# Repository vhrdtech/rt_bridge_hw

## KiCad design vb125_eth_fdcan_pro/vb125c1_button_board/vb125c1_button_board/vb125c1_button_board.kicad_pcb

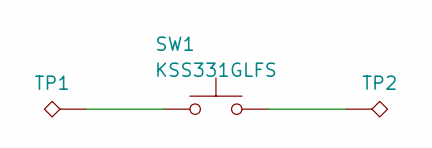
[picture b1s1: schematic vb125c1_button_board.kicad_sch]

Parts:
SW1: KSS331GLFS; SW_KSS3
TP1, TP2: TestPoint_Alt; TestPoint_Pad_4.0x4.0mm

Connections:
unnamed: SW1.1, TP1.1
unnamed: SW1.2, TP2.1

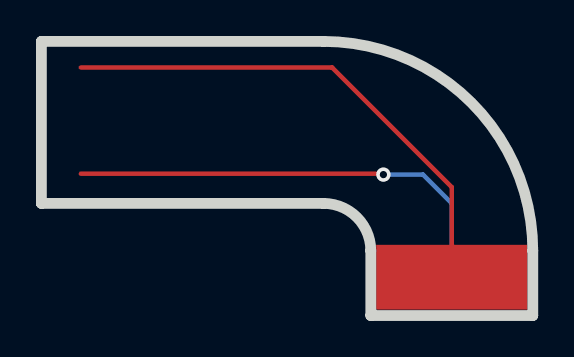
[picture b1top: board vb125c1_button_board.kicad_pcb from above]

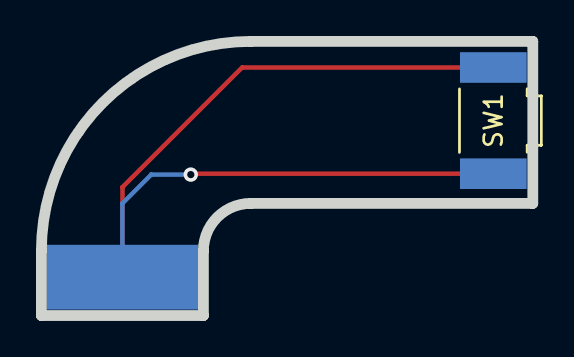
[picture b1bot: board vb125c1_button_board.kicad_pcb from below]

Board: 2 copper layers, 27.3 x 15.2 mm, 3 parts (2 on the bottom side), 2 nets.

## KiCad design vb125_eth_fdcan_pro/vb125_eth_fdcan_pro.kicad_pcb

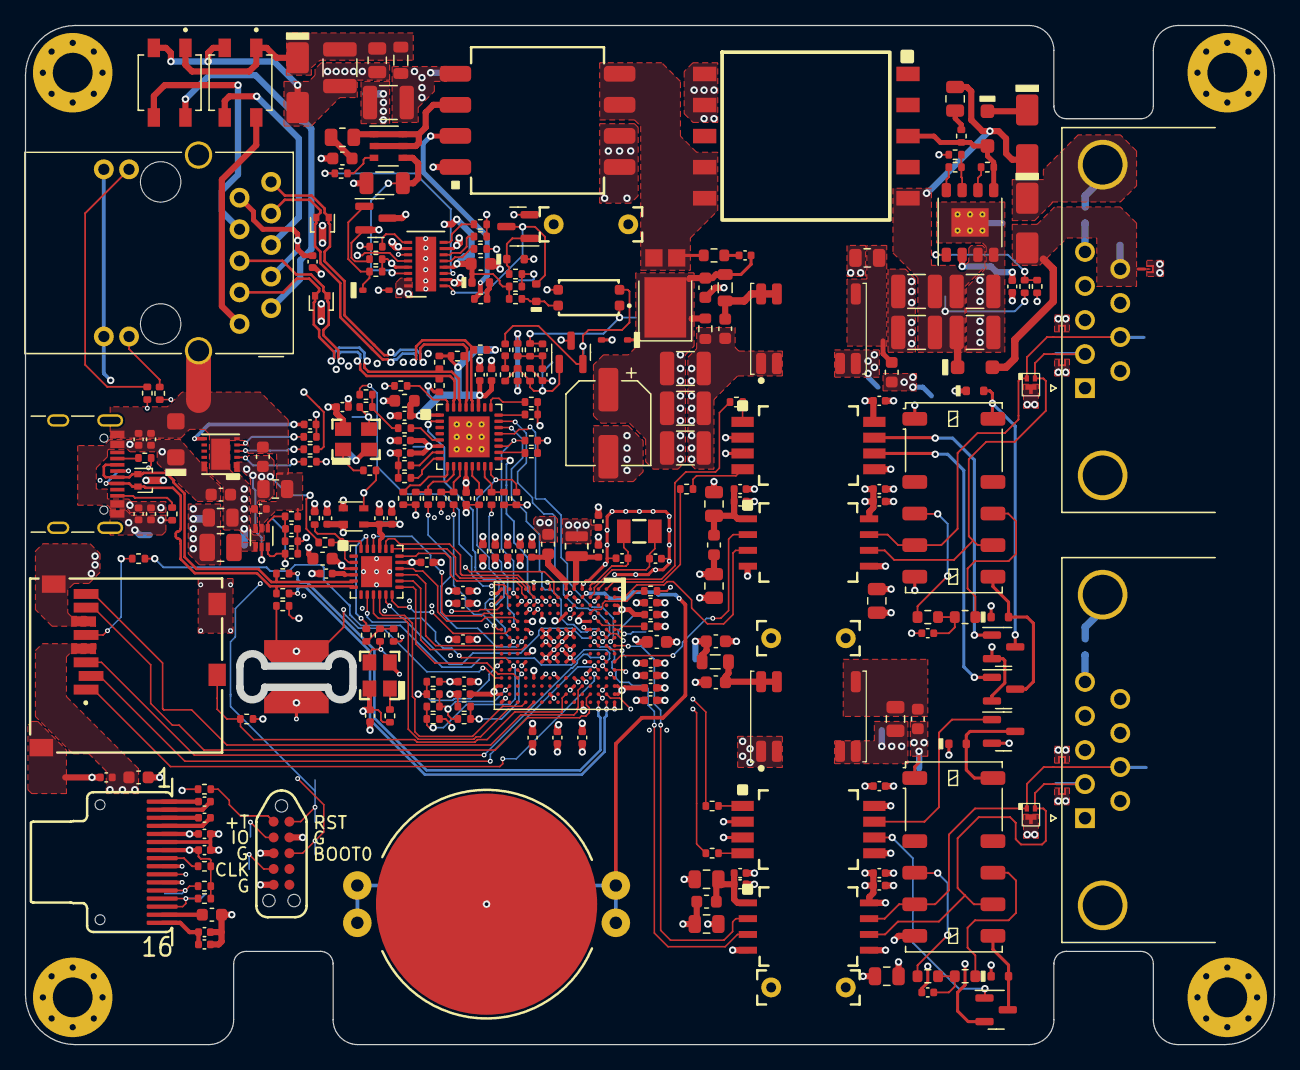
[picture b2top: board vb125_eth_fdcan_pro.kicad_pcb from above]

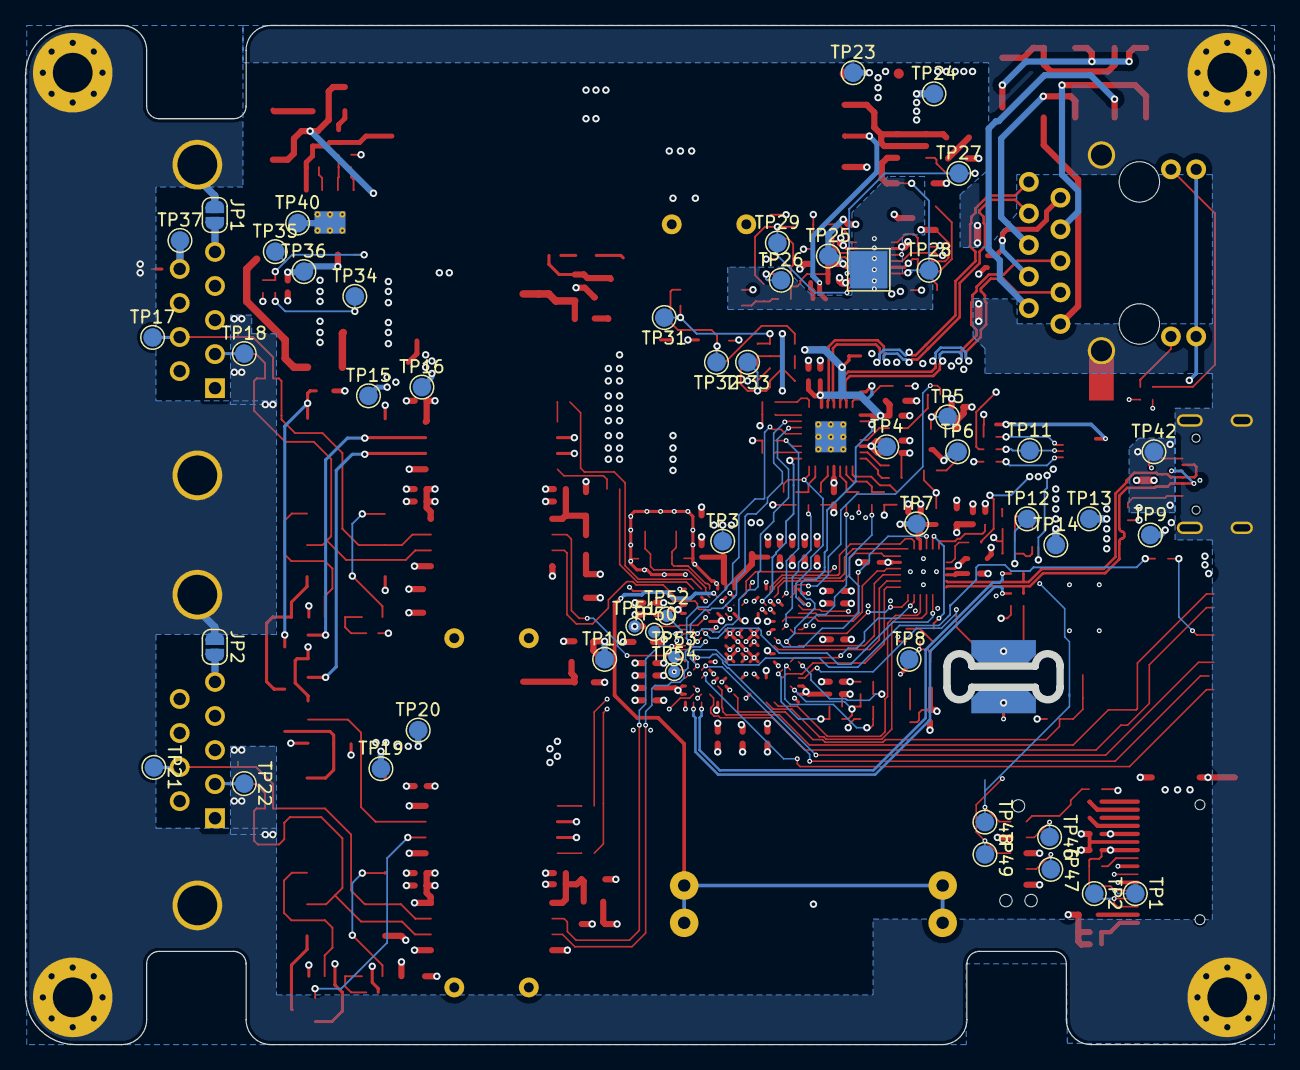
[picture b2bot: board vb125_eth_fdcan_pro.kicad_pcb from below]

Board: 6 copper layers, 100.5 x 82.0 mm, 329 parts (50 on the bottom side), 201 nets.

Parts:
B1: BAT-HLD-001-THM
C1, C5, C15, C18, C37, C95: 4.7uF; C_0402_1005Metric
C2, C4, C9, C11, C12, C13, C14, C16, C19, C21, C23, C24, C26, C28, C29, C32, C33, C34, C47, C50, C56, C61, C67, C70, C75, C81, C84: 100nF; C_0402_1005Metric
C3: 2.2uF; C_0603_1608Metric
C6, C7, C22, C25, C35, C41, C42, C51, C94, C108: 1uF; C_0402_1005Metric
C8, C10, C44, C62, C64, C76, C78, C90: 4.7uF; C_0603_1608Metric
C17, C20: 12pF; C_0402_1005Metric
C27, C31: 10uF; C_0402_1005Metric
C30: 220pF; C_0402_1005Metric
C36, C96: 470pF; C_0402_1005Metric
C38, C43, C45, C46, C48, C49, C63, C68, C77, C82: 10nF; C_0402_1005Metric
C40: 22nF; C_0402_1005Metric
C52: >10uF; C_0603_1608Metric
C53: 3.3nF; C_0402_1005Metric
C54: DNP; C_0603_1608Metric
C55, C58, C60, C69, C71, C74, C83, C85: 10uF; C_0805_2012Metric
C57: DNP; C_0402_1005Metric
C59, C73: DNP; C_0805_2012Metric
C65, C79, C92: Y rated, THT; C_Disc_D7.0mm_W2.5mm_P6.00mm
C72, C86: 4n7; C_0402_1005Metric
C87, C101, C102, C104, C106: 4.7uF; C_1210_3225Metric
C88: 100nF; C_0805_2012Metric
C89: 1uF; C_1210_3225Metric
C91: 68pF; C_0603_1608Metric
C97: 33nF; C_0402_1005Metric
C99: 27nF; C_0402_1005Metric
C100: 220uF?; CP_Elec_6.3x7.7
C110: 220pF; C_0805_2012Metric
C112, C113, C114: 100uF; C_1210_3225Metric
D1, D16, D21: RCLAMP0502BA; SOT-416
D2: SMF22A; D_SMF
D3, D4, D6, D7, D13, D14, D15: BAS516; D_SOD-523
D5, D8: PESD2CANFD24V-QBZ; DFN1110D-3_3-XDFN
D9, D10: HDS10M-13; DIOB_HDS10M-13
D11: SMAJ58A; D_SMA
D12: MMSZ5237BS-7-F; D_SOD-323
D17: buspower_iso: SMAJ58CA; buspower_dc: SMAJ36CA; D_SMA
D18, D20: RB168MM150TFTR; D_SOD-123F
D19: CMZ5944B; D_SMA
D22: PDS360-13; D_PowerDI-5
D23: 5V6?; D_SOD-323
E1, E2, E3, E4, E5: SparkGap; SPARK_GAP_011
FB1: FBMJ1608HM180NTR; L_0603_1608Metric
FB2: MH1608-601Y; L_0603_1608Metric
FB3, FB4, FB5, FB6: BLM18HE152SN1D; L_0603_1608Metric
H1, H2, H3, H4: MountingHole_Pad; MountingHole_3.2mm_M3_Pad_Via
HS1: Heatsink_Pad; TestPoint_Pad_3.0x3.0mm
J1: MEM2061-01-188-00-A; MEM2061
J2: TAGconnect NL; TC2050-IDC-NL
J4: ARJM11D7-114-AB; ARJM11D7-114-AB-EW2
J5: USB_C_Receptacle_USB2.0; USB_C_Receptacle_GCT_USB4105-xx-A_16P_TopMnt_Horizontal
J6, J7: D09P33E4GL00LF
JP1, JP2: SolderJumper_2_Open; SolderJumper-2_P1.3mm_Open_RoundedPad1.0x1.5mm
K1, K2: EE2-4.5TNUH; Relay_DPDT_Kemet_EE2_NUH_DoubleCoil
L1: LQM2MPN2R2NG0; MURATA_LQM2
L2: DFE252010F-1R0M=P2; L_1008_2520Metric
L3, L4: 6.8uH; L_0805_2012Metric
L5: 3.3uH; L_0805_2012Metric
M1: DM-OLED042-647; DM-OLED042-647-TOP
M2, M3: B0505MT-1WR4
NT1: NetTie_2; NetTie-2_SMD_Pad2.0mm
Q1, Q2, Q3, Q4: BSS138; SOT-23
Q5: MMBTA42; SOT-23
Q6: Si3440DV; TSOP-6_1.65x3.05mm_P0.95mm
Q7: 2N7002; SOT-23
R1, R2: 3K3; R_0402_1005Metric
R5, R8, R10, R57, R58, R76, R86: 100K; R_0402_1005Metric
R6: RID_PRODUCT; R_0402_1005Metric
R7, R12, R13, R17, R18, R51, R52, R75, R93: 10K; R_0402_1005Metric
R9: RID_REV; R_0402_1005Metric
R11: RID_BOM; R_0402_1005Metric
R14, R21, R22, R23: 33R; R_0402_1005Metric
R15, R35, R36, R38, R39: 49R9; R_0402_1005Metric
R16, R55: 0; R_0402_1005Metric
R19, R20, R24, R26, R27, R29, R30, R31, R32, R33, R34, R37, R47, R60: 10k; R_0402_1005Metric
R25: 1k5; R_0402_1005Metric
R28: 12k1; R_0402_1005Metric
R40, R41, R42, R50, R53, R54, R92: ?R; R_0402_1005Metric
R43, R44, R61, R62, R65, R66, R83: 1K; R_0402_1005Metric
R45, R46: 5K1; R_0402_1005Metric
R48, R49: 39R; R_0402_1005Metric
R56: 301K; R_0402_1005Metric
R59: 45k; R_0402_1005Metric
R63, R64, R67, R68: 60R4; R_0603_1608Metric
R69, R70, R71, R72: DNP; R_0402_1005Metric
R73, R74: 220K; R_0402_1005Metric
R77: 100R; R_0805_2012Metric
R78: 4K7; R_0402_1005Metric
R79: 0.125R; R_1206_3216Metric
R80: 6K8; R_0402_1005Metric
R81: 510R; R_0402_1005Metric
R82: 10R; R_0603_1608Metric
R84: 470R; R_0402_1005Metric
R85: 47K; R_0402_1005Metric
R87: 33K2; R_0402_1005Metric
R89: 1M; R_0402_1005Metric
R90: 348K; R_0402_1005Metric
R94: 100R; R_0402_1005Metric
R95: 158K; R_0402_1005Metric
R98: 250R; R_0603_1608Metric
T1: PA1134NL
T2: 750315125
TP1, TP2, TP3, TP4, TP5, TP6, TP7, TP8, TP9, TP10, TP11, TP12, TP13, TP14, TP15, TP16, TP17, TP18, TP19, TP20, TP21, TP22, TP23, TP24, TP25, TP26, TP27, TP28, TP29, TP31, TP32, TP33, TP34, TP35, TP36, TP37, TP40, TP42, TP46, TP47, TP48, TP49: TestPoint_Probe; TestPoint_Pad_D1.5mm
TP50, TP51, TP52, TP53, TP54: TestPoint; TestPoint_Pad_D1.0mm
U1: STM32H725IGKx; UFBGA-201_10x10mm_Layout15x15_P0.65mm
U2: LAN8740A; QFN-32-1EP_5x5mm_P0.5mm_EP3.3x3.3mm_ThermalVias
U3: NCP563SQ18T1G; SC-82AB
U4: USB3315; QFN24_MICROCHIP
U5: AOZ1376DI-02; DFN-12-AOZ
U6: RT5760A/B; SOT-563
U7, U9: ADM3050EBRIZ; RI-8-1_ADI
U8, U10: TLP2270; SO8L_TOS
U11: LTC4267; DFN-16-1EP_3x5mm_P0.5mm_EP1.66x4.4mm
U12: PS2911-1-F3-AX; PS2911
U13: ZR431; SOT-23
U15: LT8304IS8E#PBF; SOIC-8-ANALOG
VB125C1: vb125c1_button_board
X1: ECX-.327-CDX-1293
X2: 50MHz; Oscillator_SMD_Abracon_ASE-4Pin_3.2x2.5mm
X3: 24MHz; Oscillator_SMD_Abracon_ASE-4Pin_3.2x2.5mm

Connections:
+3V3_DCDC: C1.1, C2.1, C8.1, C9.1, C10.1, C11.1, C12.1, C13.1, C14.1, C16.1, C19.1, C21.1, C23.1, C25.1, C26.1, C28.1, C32.1, C38.1, C41.1, C44.1, C45.1, C47.1, C57.1, C58.1, C59.1, C73.1, FB1.1, FB2.1, FB3.1, FB5.1, J1.4 (VDD), L2.2, M1.5 (VBAT), M1.7 (VDD), R1.1, R2.1, R7.1, R12.1, R13.1, R15.1, R16.1, R17.1, R24.1, R25.1, R26.1, R27.1, R29.1, R30.1, R32.1, R37.2, R47.2, R58.2, R59.2, TP13.1, U1.D5 (VDD), U1.D11 (VDD), U1.E4 (VDD), U1.E12 (VDD), U1.E15 (VDD50USB), U1.F13 (VDD33USB), U1.G4 (VDD), U1.H12 (VDD), U1.K4 (VDD), U1.L12 (VDD), U1.M5 (VDD), U1.M9 (VDD), U2.12 (VDDIO), U3.2 (VIN), U3.4 (EN), U4.3 (VBAT), U4.17 (VDDIO), X2.4 (Vdd), X3.4 (Vdd)
+5V0_SYS: C54.1, C55.1, C56.1, C62.1, C76.1, C96.2, C100.1, C112.1, C113.1, C114.1, D22.1 (K), D23.1 (K), L3.1, L4.1, R51.1, R57.2, R84.2, R86.1, R98.1, TP10.1, U5.1 (VOUT), U5.2 (VOUT), U6.3 (VIN), U6.5 (EN)
+VIN_USB: C43.1, C46.1, C48.1, C49.1, C52.1, D2.1 (A1), J5.A4 (VBUS), J5.A9 (VBUS), J5.B4 (VBUS), J5.B9 (VBUS), TP42.1, U5.11 (VIN), U5.12 (VIN)
/Bus Power/+VIN_DB9: D17.2 (A2), D18.2 (A), E5.1, J6.9, TP37.1
/Bus Power/+VIN_DB9_PR: C101.1, C102.1, C104.1, C106.1, C110.1, D18.1 (K), D19.2 (A), R89.1, T2.5, TP34.1, U15.3 (VIN)
/Bus Power/BP_EN_UVLO: R89.2, R90.1, TP35.1, U15.1 (EN/UVLO)
/Bus Power/BP_INT_VCC: C108.1, TP36.1, U15.2 (INT_VCC)
/Bus Power/BP_RFB: R95.2, U15.6 (RFB)
/Bus Power/BP_RREF: R92.1, R93.1, U15.7 (RREF)
/Bus Power/BP_SW: D20.2 (A), R94.2, R95.1, T2.3, U15.5 (SW)
/Bus Power/BP_TC: R92.2, U15.8 (TC)
/Bus Power/RECT_COMMON: D22.2 (A), R82.1, T1.5, T1.6, T2.6, T2.7
/CAN Ch1/+5V0_ISO: C67.1, C68.1, C70.1, C71.1, D3.1 (K), D4.1 (K), FB4.2, K1.1, K1.6, TP15.1, U7.8 (VDD2), U8.8 (VDD)
/CAN Ch1/+5V0_MFLT: C64.1, L3.2, M2.13 (VIN), M2.14 (VIN)
/CAN Ch1/+VO: C69.1, FB4.1, M2.8 (+VO)
/CAN Ch1/CAN_H: D5.1 (A1), E1.1, J6.7, K1.5, TP17.1, U7.7 (CANH)
/CAN Ch1/CAN_L: D5.2 (A2), E3.1, J6.2, K1.8, TP18.1, U7.6 (CANL)
/CAN Ch1/CT_AR: R62.2, U8.4
/CAN Ch1/CT_AS: R61.2, U8.1
/CAN Ch1/CT_GR: Q2.1 (G), U8.6
/CAN Ch1/CT_GS: Q1.1 (G), U8.7
/CAN Ch1/FDCAN_RX: U1.A2 (PB8), U7.3 (RXD)
/CAN Ch1/FDCAN_TX: U1.A10 (PD1), U7.2 (TXD)
/CAN Ch1/TERM_DIS: R62.1, U1.B1 (PE4)
/CAN Ch1/TERM_EN: R61.1, U1.C1 (PC13)
/CAN Ch2/+5V0_ISO: C81.1, C82.1, C84.1, C85.1, D6.1 (K), D7.1 (K), FB6.2, K2.1, K2.6, TP19.1, U9.8 (VDD2), U10.8 (VDD)
/CAN Ch2/+5V0_MFLT: C78.1, L4.2, M3.13 (VIN), M3.14 (VIN)
/CAN Ch2/+VO: C83.1, FB6.1, M3.8 (+VO)
/CAN Ch2/CAN_H: D8.1 (A1), E2.1, J7.7, K2.5, TP21.1, U9.7 (CANH)
/CAN Ch2/CAN_L: D8.2 (A2), E4.1, J7.2, K2.8, TP22.1, U9.6 (CANL)
/CAN Ch2/CT_AR: R66.2, U10.4
/CAN Ch2/CT_AS: R65.2, U10.1
/CAN Ch2/CT_GR: Q4.1 (G), U10.6
/CAN Ch2/CT_GS: Q3.1 (G), U10.7
/CAN Ch2/FDCAN_RX: U1.C8 (PG10), U9.3 (RXD)
/CAN Ch2/FDCAN_TX: U1.A8 (PG9), U9.2 (TXD)
/CAN Ch2/ISO: C79.2, C81.2, C82.2, C83.2, C84.2, C85.2, C86.2, J7.3, J7.6, M3.6 (0V), M3.7 (0V), Q3.2 (S), Q4.2 (S), TP20.1, U9.5 (GND2), U10.5 (GND)
/CAN Ch2/TERM_DIS: R66.1, U1.C14 (PA10)
/CAN Ch2/TERM_EN: R65.1, U1.B14 (PA8)
/Eth/+AVDD_PHY: C33.1, C34.1, C37.1, C40.1, FB2.2, J4.4 (RCT), J4.9 (TCT), R35.1, R36.1, R38.1, R39.1, U2.1 (VDD2A), U2.27 (VDD1A)
/Eth/PHYAD0: R31.1, U2.13 (RXER/RXD4/PHYAD0)
/Eth/PHYAD1: R34.1, U2.7 (RXCLK/PHYAD1)
/Eth/PHYAD2: R33.1, U2.8 (RXD3/PHYAD2)
/Eth/RBIAS: R28.1, U2.32 (RBIAS)
/Eth/RD_N: D1.2 (K2), J4.3 (RD-), R35.2, U2.30 (RXN)
/Eth/RD_P: D1.1 (K1), J4.5 (RD+), R36.2, U2.31 (RXP)
/Eth/RXD0: R21.2, R29.2, U2.11 (RXD0/MODE0)
/Eth/RXD1: R22.2, R27.2, U2.10 (RXD1/MODE1)
/Eth/RXD2_NU: R30.2, U2.9 (RXD2/~PME/RMIISEL)
/Eth/TD_N: D21.2 (K2), J4.8 (TD-), R38.2, U2.28 (TXN)
/Eth/TD_P: D21.1 (K1), J4.10 (TD+), R39.2, U2.29 (TXP)
/Eth/TXD2_NU: R19.2, U2.24 (TXD2)
/Eth/TXD3_NU: R20.2, U2.25 (TXD3)
/Eth/VDDCR_PHY: C35.1, C36.1, TP4.1, U2.6 (VDDCR)
/MCU_H7/+VCC_OLED: C4.1, C5.1, M1.16 (VCC)
/MCU_H7/+VCOMH_OLED: C3.1, M1.15 (VCOMH)
/MCU_H7/BOOT0: J2.8, R18.1, TP49.1, U1.C5 (BOOT0)
/MCU_H7/BUTTON: R12.2, U1.R12 (PE11), VB125C1.2
/MCU_H7/H7_SWCLK: J2.4, TP47.1, U1.A12 (PA14)
/MCU_H7/H7_SWDIO: J2.2, TP46.1, U1.B13 (PA13)
/MCU_H7/I2C2_SCL: M1.12 (D0), R2.2, TP1.1, U1.F3 (PF1)
/MCU_H7/I2C2_SDA: M1.13 (D1), M1.14 (D2), R1.2, TP2.1, U1.F4 (PF0)
/MCU_H7/OLED_RST: M1.10 (~RESET), U1.R3 (PA0_C)
/MCU_H7/OSC32_IN: C17.1, U1.D2 (PC14-OSC32_IN), X1.1
/MCU_H7/OSC32_OUT: C20.1, U1.D1 (PC15-OSC32_OUT), X1.2
/MCU_H7/RID_BOM: R10.2, R11.1, U1.R10 (PF14)
/MCU_H7/RID_EN: R5.1, R8.1, R10.1, U1.P13 (PE13)
/MCU_H7/RID_PRODUCT: R5.2, R6.1, U1.P11 (PF12)
/MCU_H7/RID_REV: R8.2, R9.1, U1.N11 (PF13)
/MCU_H7/SDMMC_CK: R14.1, U1.B11 (PC12)
/MCU_H7/SDMMC_CKJ: J1.5 (CLK), R14.2
/MCU_H7/SDMMC_CMD: J1.3 (CMD), U1.B10 (PD2)
/MCU_H7/SDMMC_D0: J1.7 (DAT0), U1.D14 (PC8)
/MCU_H7/SDMMC_D1: J1.8 (DAT1), U1.E13 (PC9)
/MCU_H7/SDMMC_D2: J1.1 (DAT2), U1.C12 (PC10)
/MCU_H7/SDMMC_D3: J1.2 (DAT3/CD), U1.C11
/MCU_H7/SDMMC_PRESENT: J1.10 (DET_A), R13.2, U1.G14 (PG4)
/MCU_H7/SPI1_MISO: TP52.1, U1.B6 (PB4)
/MCU_H7/SPI1_MOSI: TP53.1, U1.B8 (PD7)
/MCU_H7/SPI1_NSS: TP54.1, U1.A11 (PA15)
/MCU_H7/SPI1_SCK: TP50.1, U1.A6 (PB3)
/MCU_H7/VBAT: B1.P, U1.E2 (VBAT)
/MCU_H7/VDDA: C22.1, C24.1, R16.2, U1.M3 (VREF+), U1.M4 (VDDA)
/MCU_H7/VDDLDO: C15.1, C18.1, C31.1, C95.1, L1.2, TP3.1, U1.A3 (VDDLDO), U1.A4 (VCAP), U1.A13 (VDDLDO), U1.A14 (VCAP), U1.G2 (VFBSMPS), U1.R13 (VCAP), U1.R14 (VDDLDO)
/MCU_H7/VDDSMPS: C27.1, FB1.2, U1.G1 (VDDSMPS)
/MCU_H7/VLX: C30.1, L1.1, U1.F1 (VLXSMPS)
/MCU_H7/~H7_RST: C29.1, J2.10, TP48.1, U1.L1 (NRST)
/PoE/POE_BR_N: C87.2, C88.2, D9.3 (-), D10.3 (-), D11.2 (A), R72.1, U11.7 (VPORTN), U11.12 (SIGDISA)
/PoE/POE_BR_P: C87.1, C88.1, D9.1 (+), D10.1 (+), D11.1 (K), L5.1
/PoE/POE_COMP: C94.1, C97.1, R83.1, R84.1
/PoE/POE_EP_THPAD: HS1.1, U11.17 (EP_FLOAT)
/PoE/POE_FB: R85.1, R86.2, R87.1, TP33.1, U13.1 (REF)
/PoE/POE_ISENSE: Q6.4 (S), R79.1, TP28.1, U11.14 (SENSE)
/PoE/POE_ITH: D15.2 (A), Q7.3 (D), TP29.1, U11.1 (ITH/RUN)
/PoE/POE_NGATE: R78.1, TP27.1, U11.3 (NGATE)
/PoE/POE_OP_A: C97.2, R83.2, TP31.1, U12.1
/PoE/POE_OP_K: C99.2, TP32.1, U12.2, U13.2 (K)
/PoE/POE_PVCC: C90.1, D13.1 (K), Q5.2 (E), R74.2, R76.2, R80.1, TP25.1, U11.4 (PVCC)
/PoE/POE_TR_SW: Q6.1 (D), Q6.2 (D), Q6.5 (D), Q6.6 (D), R77.2, T1.3
/PoE/POE_VPORTP: C89.1, C91.1, L5.2, Q5.3 (C), R73.1, R74.1, T1.4, TP23.1, U11.13 (VPORTP)
/PoE/~POE_PWRGD: R75.1, R76.1, TP26.1, U11.11 (~PWRGD)
/Power/3V3_FB: C57.2, R59.1, R60.2, U6.1 (FB)
/Power/3V3_PG: R58.1, TP12.1, U6.6 (PG)
/Power/3V3_SW: L2.1, U6.4 (SW)
/Power/AOZ_ENB: R55.1, U5.5 (ENB)
/Power/AOZ_POVP: R56.1, U5.3 (POVP)
/Power/AOZ_SS: C53.1, U5.7 (SS)
/Power/VUSB_FLTB: R57.1, TP11.1, U5.4 (FLTB)
/USB/+1V8_ULPI: C42.1, C50.1, TP7.1, U3.3 (VOUT), U4.21 (VDD1.8)
/USB/CC1: J5.A5 (CC1), R45.1
/USB/CC2: J5.B5 (CC2), R46.1
/USB/D_N: D16.1 (K1), J5.A7 (D-), J5.B7 (D-), R48.1, U4.5 (DM)
/USB/D_P: D16.2 (K2), J5.A6 (D+), J5.B6 (D+), R49.2, U4.6 (DP)
/USB/ULPI_RBIAS: R52.1, U4.24 (RBIAS)
/USB/ULPI_REGOUT_3V3: C51.1, U4.4 (VDD3.3)
/USB/ULPI_VBUS: R51.2, U4.2 (VBUS)
CHASSIS: D1.3 (A), D5.3 (common), D8.3 (common), D16.3 (A), D17.1 (A1), D21.3 (A), E1.2, E2.2, E3.2, E4.2, E5.2, H1.1, H2.1, H3.1, H4.1, J4.SH (SHIELD), J5.S1 (SHIELD), J6.0 (PAD), J7.0 (PAD), JP1.1 (A), JP2.1 (A), NT1.1
ETH_CRS_DV: R23.1, U1.N6 (PA7)
ETH_MDC: U1.L3 (PC1), U2.17 (MDC)
ETH_MDIO: R25.2, U1.R2 (PA2), U2.16 (MDIO)
ETH_REFCLK: R42.2, U1.P2 (PA1)
ETH_RXD0: R21.1, U1.R6 (PC4)
ETH_RXD1: R22.1, U1.M7 (PC5)
ETH_TXD0: U1.B7 (PG13), U2.22 (TXD0)
ETH_TXD1: U1.C7 (PG14), U2.23 (TXD1)
ETH_TXEN: U1.A7 (PG11), U2.21 (TXEN)
GND: B1.M, C1.2, C2.2, C3.2, C4.2, C5.2, C8.2, C9.2, C10.2, C11.2, C12.2, C13.2, C14.2, C15.2, C16.2, C17.2, C18.2, C19.2, C20.2, C21.2, C22.2, C23.2, C24.2, C25.2, C26.2, C27.2, C28.2, C29.2, C30.2, C31.2, C32.2, C33.2, C34.2, C35.2, C36.2, C37.2, C38.2, C40.2, C41.2, C42.2, C43.2, C44.2, C45.2, C46.2, C47.2, C48.2, C49.2, C50.2, C51.2, C52.2, C53.2, C54.2, C55.2, C56.2, C58.2, C59.2, C60.2, C61.2, C62.2, C63.2, C64.2, C65.1, C73.2, C74.2, C75.2, C76.2, C77.2, C78.2, C79.1, C92.2, C94.2, C95.2, C100.2, C112.2, C113.2, C114.2, D2.2 (A2), D23.2 (A), J1.6 (VSS), J1.9 (DET_B), J1.11 (SHIELD), J2.3, J2.5, J2.9, J4.12 (GK), J4.14 (YK), J5.A1 (GND), J5.A12 (GND), J5.B1 (GND), J5.B12 (GND), M1.6 (VSS), M1.9 (CS), M1.11 (DC), M2.1 (GND), M2.2 (GND), M3.1 (GND), M3.2 (GND), NT1.2, R6.2, R9.2, R11.2, R18.2, R19.1, R20.1, R28.2, R31.2, R33.2, R34.2, R45.2, R46.2, R52.2, R55.2, R56.2, R60.1, R87.2, R98.2, T1.7, T1.8, T2.9, T2.10, TP6.1, TP9.1, TP14.1, TP51.1, U1.A1 (VSS), U1.A15 (VSS), U1.C2 (VSS), U1.D6 (VSS), U1.D10 (VSS), U1.E1 (VSS), U1.F2 (VSSSMPS), U1.F6 (VSS), U1.F7 (VSS), U1.F8 (VSS), U1.F9 (VSS), U1.F10 (VSS), U1.F12 (VSS), U1.G6 (VSS), U1.G7 (VSS), U1.G8 (VSS), U1.G9 (VSS), U1.G10 (VSS), U1.H6 (VSS), U1.H7 (VSS), U1.H8 (VSS), U1.H9 (VSS), U1.H10 (VSS), U1.J6 (VSS), U1.J7 (VSS), U1.J8 (VSS), U1.J9 (VSS), U1.J10 (VSS), U1.J14 (VSS), U1.K2 (VSS), U1.K6 (VSS), U1.K7 (VSS), U1.K8 (VSS), U1.K9 (VSS), U1.K10 (VSS), U1.K12 (VSS), U1.L4 (VREF-), U1.M6 (VSS), U1.M10 (VSS), U1.N3 (VSSA), U1.R1 (VSS), U1.R15 (VSS), U2.33 (VSS), U3.1 (GND), U4.25 (GND), U5.6 (GND), U5.13 (EP_GND), U6.2 (GND), U7.4 (GND1), U8.2, U8.3, U9.4 (GND1), U10.2, U10.3, U13.3 (A), VB125C1.1, X2.2 (GND), X3.2 (GND)
H7_CLK: R54.2, U1.J1 (PH0-OSC_IN)
ISO_1: C65.2, C67.2, C68.2, C69.2, C70.2, C71.2, C72.2, C101.2, C102.2, C104.2, C106.2, C108.2, J6.3, J6.6, M2.6 (0V), M2.7 (0V), Q1.2 (S), Q2.2 (S), R90.2, R93.2, TP16.1, TP40.1, U7.5 (GND2), U8.5 (GND), U15.4 (GND), U15.9 (GND)
ISO_POE: C89.2, C90.2, C92.1, D12.2 (A), D14.2 (A), Q7.2 (S), R69.1, R70.1, R71.1, R79.2, T1.1, TP24.1, U11.2 (PGND), U11.10 (POUT), U11.15 (PGND), U11.16 (VFB), U12.3
unnamed: C72.1, R63.2, R64.2
unnamed: C86.1, R67.2, R68.2
unnamed: C91.2, R77.1
unnamed: C96.1, R82.2
unnamed: C99.1, R85.2
unnamed: C110.2, R94.1
unnamed: D3.2 (A), K1.12, Q1.3 (D)
unnamed: D4.2 (A), K1.7, Q2.3 (D)
unnamed: D6.2 (A), K2.12, Q3.3 (D)
unnamed: D7.2 (A), K2.7, Q4.3 (D)
unnamed: D12.1 (K), Q5.1 (B), R73.2
unnamed: D13.2 (A), R81.1
unnamed: D14.1 (K), Q7.1 (G), R75.2
unnamed: D15.1 (K), R80.2, U12.4
unnamed: D19.1 (K), D20.1 (K)
unnamed: J2.1, R15.2
unnamed: J4.11 (GA), R44.1
unnamed: J4.13 (YA), R43.1
unnamed: J6.5, JP1.2 (B)
unnamed: J7.5, JP2.2 (B)
unnamed: K1.4, R63.1
unnamed: K1.9, R64.1
unnamed: K2.4, R67.1
unnamed: K2.9, R68.1
unnamed: M1.8 (BS1), R7.2
unnamed: C7.2, M1.4 (C1N)
unnamed: C7.1, M1.3 (C1P)
unnamed: C6.2, M1.2 (C2N)
unnamed: C6.1, M1.1 (C2P)
unnamed: Q6.3 (G), R78.2
unnamed: R40.2, R41.1, R42.1
unnamed: R50.2, R53.1, R54.1
unnamed: R69.2, U11.6 (NC)
unnamed: R70.2, U11.8 (NC)
unnamed: R71.2, U11.9 (NC)
unnamed: R81.2, T1.2
unnamed: R17.2, U1.D4 (PDR_ON)
unnamed: R23.2, R24.2, U2.15 (COL/CRS_DV/MODE2)
unnamed: R41.2, U2.5 (XTAL1/CLKIN)
unnamed: R32.2, U2.18 (~INT/TXER/TXD4)
unnamed: R53.2, U4.23 (REFCLK)
unnamed: C60.1, C61.1, C63.1, FB3.2, U7.1 (VDD1)
unnamed: C74.1, C75.1, C77.1, FB5.2, U9.1 (VDD1)
unnamed: R72.2, U11.5 (RCLASS)
unnamed: R37.1, X2.1 (EN)
unnamed: R40.1, TP5.1, X2.3 (OUT)
unnamed: R47.1, X3.1 (EN)
unnamed: R50.1, TP8.1, X3.3 (OUT)
POE_AC1: D9.4, J4.7 (VC1+)
POE_AC2: D9.2, J4.2 (VC1-)
POE_AC3: D10.4, J4.6 (VC2+)
POE_AC4: D10.2, J4.1 (VC2-)
RJ45_LEDG: R43.2, U1.H2 (PF4)
RJ45_LEDY: R44.2, U1.H3 (PF5)
ULPI_CK: U1.P6 (PA5), U4.12 (CLKOUT)
ULPI_D0: U1.N5 (PA3), U4.16 (DATA0)
ULPI_D1: U1.R8 (PB0), U4.15 (DATA1)
ULPI_D2: U1.M8 (PB1), U4.14 (DATA2)
ULPI_D3: U1.N12 (PB10), U4.13 (DATA3)
ULPI_D4: U1.P10 (PB11), U4.11 (DATA4)
ULPI_D5: U1.M15 (PB12), U4.10 (DATA5)
ULPI_D6: U1.L15 (PB13), U4.9 (DATA6)
ULPI_D7: U1.C6 (PB5), U4.8 (DATA7)
ULPI_DIR: U1.M1 (PC2), U4.19 (DIR)
ULPI_NXT: U1.M2 (PC3), U4.18 (NXT)
ULPI_RST: U1.R4 (PH3), U4.22 (RESETB)
ULPI_STP: U1.L2 (PC0), U4.20 (STP)
USBFS_D_N: R48.2, U1.C15 (PA11)
USBFS_D_P: R49.1, U1.B15 (PA12)
~ETH_INT_PME: U1.P8 (PG0), U2.2 (LED2/~INT/~PME/~INTSEL)
~ETH_PHY_RST: R26.2, U1.N2 (PC3_C), U2.19 (~RST)

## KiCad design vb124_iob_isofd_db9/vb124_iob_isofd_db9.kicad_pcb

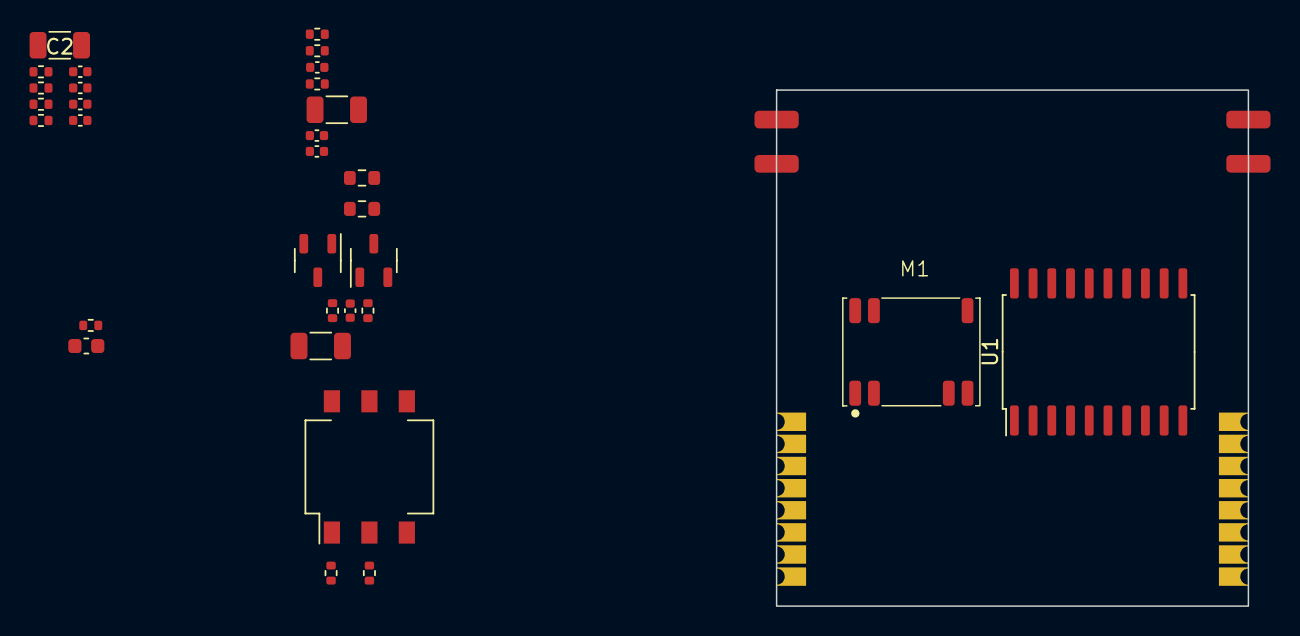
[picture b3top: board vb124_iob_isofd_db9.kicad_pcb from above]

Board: 2 copper layers, 32.0 x 35.0 mm, 32 parts (0 on the bottom side), 19 nets, no tracks yet.

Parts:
C1, C4: X7R_10nF_50V; C_0402_1005Metric
C2, C9, C12: 10.0uF ±10% 10V X7R; C_1206_3216Metric
C3, C5: 50V_100nF_X7R; C_0402_1005Metric
C6: 10.0nF ±10% 50V X7R; C_0402_1005Metric
C7: 0.1uF 10% X7R 50V; C_0402_1005Metric
C8: 220.0nF ±10% 10V X7R; C_0402_1005Metric
C10: 5.0pF; C_0402_1005Metric
C11: 4.7uF ±10% 6.3V; C_0603_1608Metric
FB1: 100MHz_1.8KOhm; R_0402_1005Metric
FB2: BLM15BX182SN1D_100MHz_1.8KOhm; R_0402_1005Metric
M1: B0505MT-1WR4
M2: iob_v2; iob_v2_module
Q1, Q2: FDN358P; SOT-23-3
R1, R2, R3, R4, R5, R8: 0; R_0402_1005Metric
R6, R7: 47K 1%; R_0402_1005Metric
R9, R12: 100K 1%; R_0402_1005Metric
R10, R11: 56R; R_0603_1608Metric
SW1: DS04-254-2-03BK-SMT; SW_DIP_SPSTx03_Slide_Omron_A6S-310x_W8.9mm_P2.54mm
U1: ADM3057E; SOIC-20W_7.5x12.8mm_P1.27mm

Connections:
+3V3_DCDC: R1.1, R3.1
+5V: C12.1, M1.8 (+VO), R8.1
+5V0_ISO: C6.1, C7.1, C9.1, FB2.2, U1.16 (VISOIN)
/CANH: R11.1, U1.14 (CANH)
/CANL: R10.1, U1.13 (CANL)
/RS: SW1.4, SW1.5, SW1.6, U1.12 (RS)
/TERM_EN_ISO: Q1.1 (G), Q2.1 (G), R9.1, U1.17 (AUXOUT)
GND: C1.2, C2.2, C3.2, C4.2, C5.2, C11.2, M1.1 (GND), M1.2 (GND), R4.2, U1.1 (GND1), U1.2 (GND1), U1.10 (GND1)
ISO: C6.2, C7.2, C8.2, C9.2, C10.2, C12.2, FB1.2, M1.6 (0V), M1.7 (0V), R5.2, R6.2, R7.2, R9.2, R12.2, SW1.3, U1.11 (GND2), U1.15 (GND2)
unnamed: C11.1, M1.13 (VIN), M1.14 (VIN), R8.2
unnamed: FB1.1, R5.1, U1.18 (GNDISO), U1.20 (GNDISO)
unnamed: Q1.3 (D), R10.2
unnamed: C10.1, Q1.2 (S), Q2.3 (D), R12.1
unnamed: Q2.2 (S), R11.2
unnamed: R6.1, SW1.1
unnamed: R7.1, SW1.2
unnamed: C2.1, C3.1, C4.1, R1.2, R2.2, U1.3 (VCC)
unnamed: C1.1, C5.1, R3.2, R4.1, U1.4 (VIO)
unnamed: C8.1, FB2.1, U1.19 (VISOOUT)

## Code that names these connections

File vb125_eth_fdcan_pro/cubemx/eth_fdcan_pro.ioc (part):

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Mcu.Name=STM32H725IGKx
Mcu.Package=UFBGA176
Mcu.UserName=STM32H725IGKx
PA1.Mode=RMII
PA1.Signal=ETH_REF_CLK
PA13(JTMS/SWDIO).Mode=Serial_Wire
PA13(JTMS/SWDIO).Signal=DEBUG_JTMS-SWDIO
PA14(JTCK/SWCLK).Mode=Serial_Wire
PA14(JTCK/SWCLK).Signal=DEBUG_JTCK-SWCLK
PA1_C.Signal=ADCx_INP1
PA2.Mode=RMII
PA2.Signal=ETH_MDIO
PA3.Mode=Device_HS
PA3.Signal=USB_OTG_HS_ULPI_D0
PA5.Mode=Device_HS
PA5.Signal=USB_OTG_HS_ULPI_CK
PA6.Signal=ADCx_INP3
PA7.Mode=RMII
PA7.Signal=ETH_CRS_DV
PA8.Mode=Clock-out-1
PA8.Signal=RCC_MCO_1
PB0.Mode=Device_HS
PB0.Signal=USB_OTG_HS_ULPI_D1
PB1.Mode=Device_HS
PB1.Signal=USB_OTG_HS_ULPI_D2
PB10.Mode=Device_HS
PB10.Signal=USB_OTG_HS_ULPI_D3
PB11.Mode=Device_HS
PB11.Signal=USB_OTG_HS_ULPI_D4
PB12.Mode=Device_HS
PB12.Signal=USB_OTG_HS_ULPI_D5
PB13.Mode=Device_HS
PB13.Signal=USB_OTG_HS_ULPI_D6
PB14.Mode=Full_Duplex_Master
PB14.Signal=SPI2_MISO
PB15.Mode=Full_Duplex_Master
PB15.Signal=SPI2_MOSI
PB3(JTDO/TRACESWO).Mode=Full_Duplex_Master
PB3(JTDO/TRACESWO).Signal=SPI1_SCK
PB4(NJTRST).Mode=Full_Duplex_Master
PB4(NJTRST).Signal=SPI1_MISO
PB5.Mode=Device_HS
PB5.Signal=USB_OTG_HS_ULPI_D7
PB8.Mode=FDCAN_Activate
PB8.Signal=FDCAN1_RX
PC0.Mode=Device_HS
PC0.Signal=USB_OTG_HS_ULPI_STP
PC1.Mode=RMII
PC1.Signal=ETH_MDC
PC10.Mode=SD_4_bits_Wide_bus
PC10.Signal=SDMMC1_D2
PC11.Mode=SD_4_bits_Wide_bus
PC11.Signal=SDMMC1_D3
PC12.Mode=SD_4_bits_Wide_bus
PC12.Signal=SDMMC1_CK
PC14-OSC32_IN.Mode=LSE-External-Clock-Source
PC14-OSC32_IN.Signal=RCC_OSC32_IN
PC2.Mode=Device_HS
PC2.Signal=USB_OTG_HS_ULPI_DIR
PC3.Mode=Device_HS
PC3.Signal=USB_OTG_HS_ULPI_NXT
PC4.Mode=RMII
PC4.Signal=ETH_RXD0
PC5.Mode=RMII
PC5.Signal=ETH_RXD1
PC8.Mode=SD_4_bits_Wide_bus
PC8.Signal=SDMMC1_D0
PC9.Mode=SD_4_bits_Wide_bus
PC9.Signal=SDMMC1_D1
PD1.Mode=FDCAN_Activate
PD1.Signal=FDCAN1_TX
PD2.Mode=SD_4_bits_Wide_bus
PD2.Signal=SDMMC1_CMD
PD3.Mode=Full_Duplex_Master
PD3.Signal=SPI2_SCK
PD7.Mode=Full_Duplex_Master
PD7.Signal=SPI1_MOSI
PF0.Mode=I2C
PF0.Signal=I2C2_SDA
PF1.Mode=I2C
PF1.Signal=I2C2_SCL
PF11.Mode=IN2-Single-Ended
PF11.Signal=ADC1_INP2
PG10.Mode=FDCAN_Activate
PG10.Signal=FDCAN3_RX
PG11.Mode=RMII
PG11.Signal=ETH_TX_EN
PG13.Mode=RMII
PG13.Signal=ETH_TXD0
PG14.Mode=RMII
PG14.Signal=ETH_TXD1
PG9.Mode=FDCAN_Activate
PG9.Signal=FDCAN3_TX
PH0-OSC_IN.Mode=HSE-External-Clock-Source
PH0-OSC_IN.Signal=RCC_OSC_IN
RCC.SYSCLKFreq_VALUE=550000000
RCC.SYSCLKSource=RCC_SYSCLKSOURCE_PLLCLK
board=custom

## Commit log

2023-03-23 Initial, create projects, setup gitignore.
2023-03-24 VB124: Work on schematic.
2023-03-29 vb125: Ethernet and H7 schematic.
2023-03-29 vb125: H7 schematic WIP.
2023-04-10 AOZ schematic. 3V3 DC-DC. Partly bus power.
2023-04-13 Work on PoE. Rearrange pages.
2023-04-14 Finish PoE schematic.
2023-04-14 vb124
2023-04-17 CAN schematics. Assign IO on H7.
2023-04-21 Finish schematics.
2023-04-21 Add testpoints and set page templates.
2023-04-25 Reimport parts onto PCB.
2023-04-25 Create _autosave-p2_mcu_h7.kicad_sch
    VB 125
2023-05-01 Preliminary floorplan
2023-05-04 Update gitignore
2023-05-06 Add sourcing information for resistors
2023-05-07 Add variants.
2023-05-11 Selection of capacitors for VB125
2023-05-20 Add missing footprints, ready to layout.
2023-05-22 Preliminary placement.
2023-05-22 Floorplan work.
2023-05-23 Continue with floorplan
2023-05-23 Add vb125c1 button board.
2023-06-03 Finish layout.
2023-06-03 Hide designators.
2023-06-14 Update sch and pcb.
2023-06-16 Update outline.
2023-07-04 Update PCB outline.
